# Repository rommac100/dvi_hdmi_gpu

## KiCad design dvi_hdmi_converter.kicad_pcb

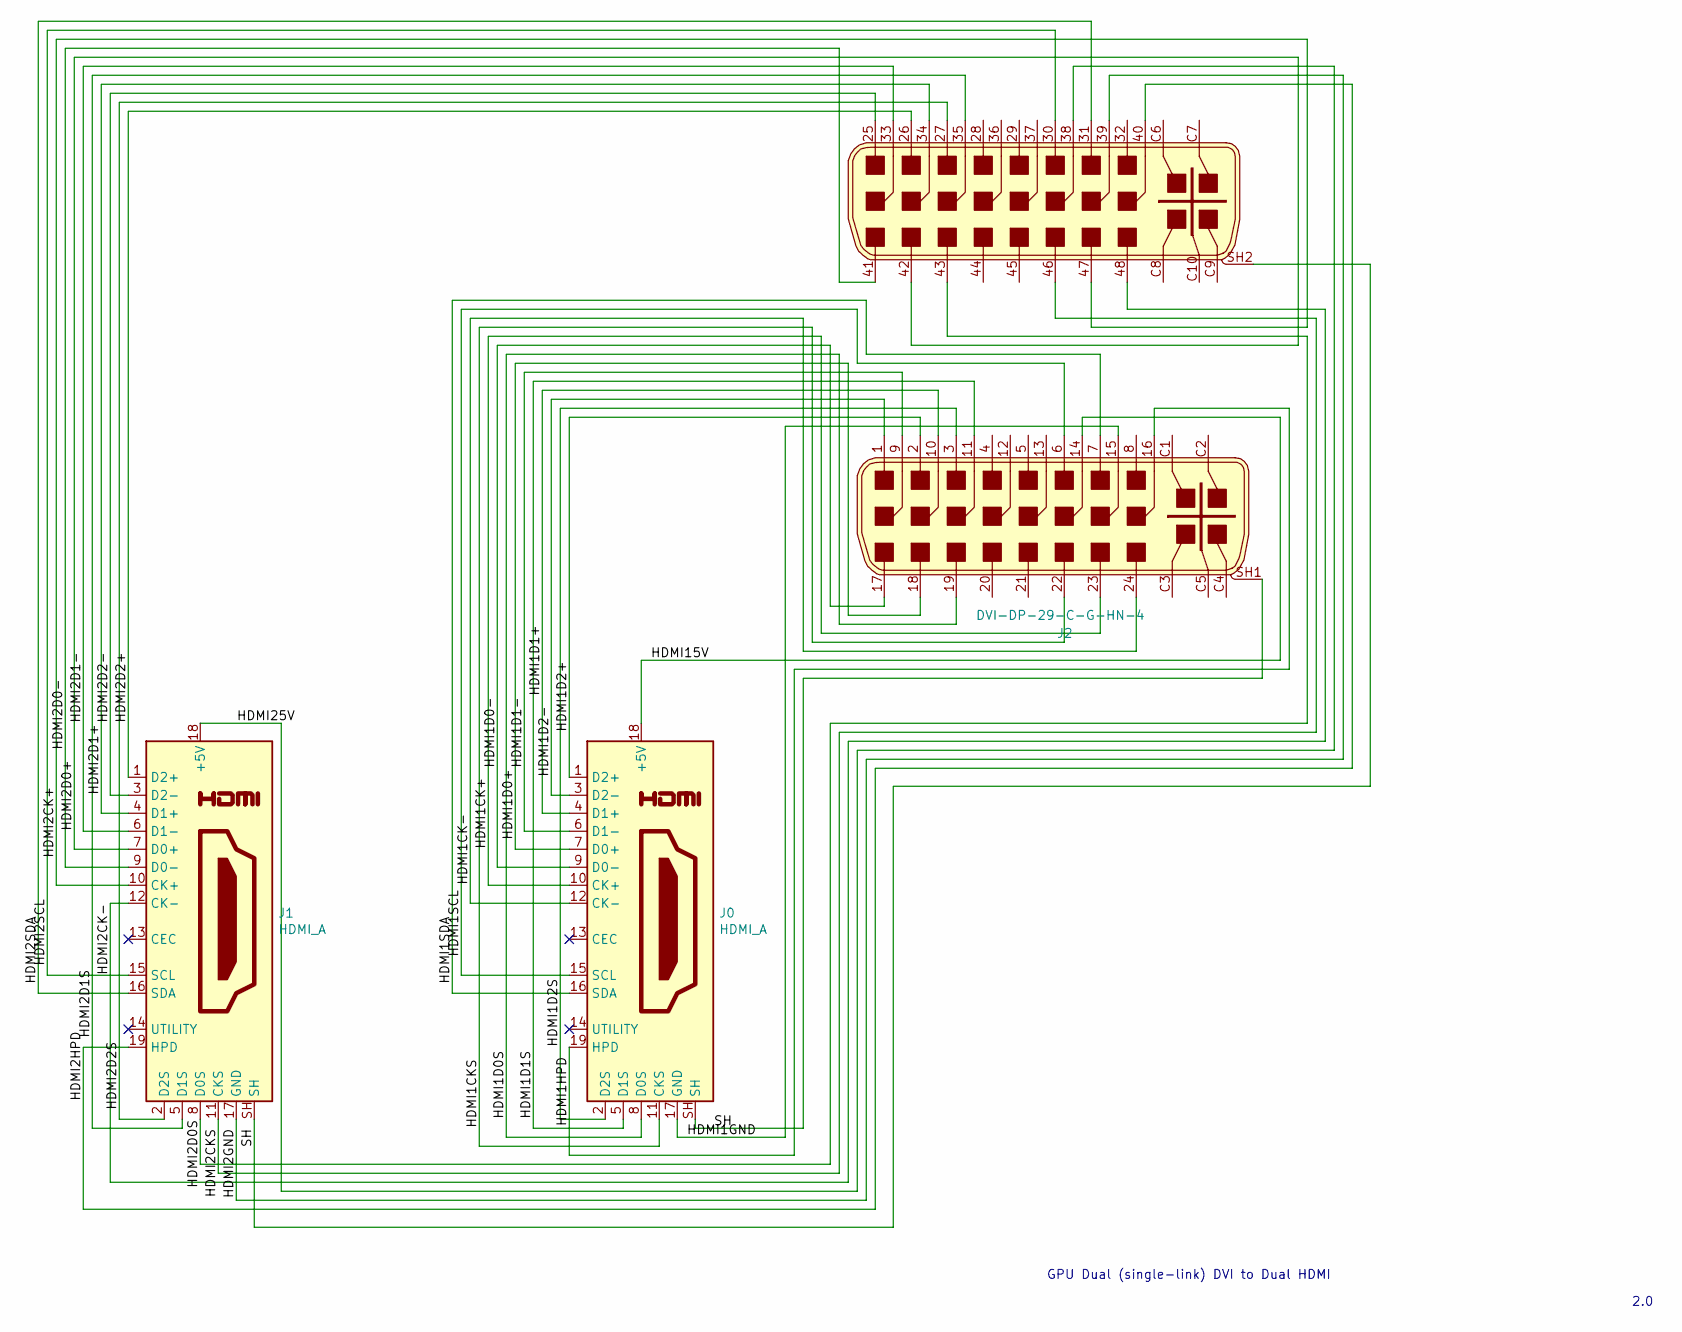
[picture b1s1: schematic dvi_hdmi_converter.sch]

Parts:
J0, J1: HDMI_A; HDMI_A_Female_2000-1-2-41-00-BK
J2: DVI-DP-29-C-G-HN-4; DVI-DP-29-C-G-HN-4-no-analog

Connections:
/HDMI1CK+: J0.10 (CK+), J2.23
/HDMI1CK-: J0.12 (CK-), J2.24
/HDMI1CKS: J0.11 (CKS), J2.22
/HDMI1D0+: J0.7 (D0+), J2.18
/HDMI1D0-: J0.9 (D0-), J2.17
/HDMI1D0S: J0.8 (D0S), J2.19
/HDMI1D1+: J0.4 (D1+), J2.10
/HDMI1D1-: J0.6 (D1-), J2.9
/HDMI1D1S: J0.5 (D1S), J2.11
/HDMI1D2+: J0.1 (D2+), J2.2
/HDMI1D2-: J0.3 (D2-), J2.1
/HDMI1D2S: J0.2 (D2S), J2.3
/HDMI1GND: J0.17 (GND), J2.15
/HDMI1HPD: J0.19 (HPD), J2.16
/HDMI1SCL: J0.15 (SCL), J2.6
/HDMI1SDA: J0.16 (SDA), J2.7
/HDMI2CK+: J1.10 (CK+), J2.47
/HDMI2CK-: J1.12 (CK-), J2.48
/HDMI2CKS: J1.11 (CKS), J2.46
/HDMI2D0+: J1.7 (D0+), J2.42
/HDMI2D0-: J1.9 (D0-), J2.41
/HDMI2D0S: J1.8 (D0S), J2.43
/HDMI2D1+: J1.4 (D1+), J2.34
/HDMI2D1-: J1.6 (D1-), J2.33
/HDMI2D1S: J1.5 (D1S), J2.35
/HDMI2D2+: J1.1 (D2+), J2.26
/HDMI2D2-: J1.3 (D2-), J2.25
/HDMI2D2S: J1.2 (D2S), J2.27
/HDMI2GND: J1.17 (GND), J2.39
/HDMI2HPD: J1.19 (HPD), J2.40
/HDMI2SCL: J1.15 (SCL), J2.30
/HDMI2SDA: J1.16 (SDA), J2.31
/HDMI15V: J0.18 (+5V), J2.14
/HDMI25V: J1.18 (+5V), J2.38
/SH: J0.SH, J1.SH, J2.SH1, J2.SH2

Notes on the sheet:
GPU Dual (single-link) DVI to Dual HDMI
2.0

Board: 4 copper layers, 3 parts (0 on the bottom side), 35 nets, no tracks yet.

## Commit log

2020-08-11 inital commit of Stacked DVI connector to dual hdmi
2020-08-11 traced out first hdmi port
2020-08-12 created first version of the layout
2020-08-24 latest update with schematic
